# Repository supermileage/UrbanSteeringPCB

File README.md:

# Urban Steering PCB

The steering wheel for the UBC Supermileage Urban Concept electric vehicle is designed to steer the vehicle, provide information to the driver, and allow the driver to control the vehicle. This repo contains the design files for the printed circuit board at the core of the steering wheel. 

Some features of this PCB:

- STM32L432 Microcontroller with built-in CAN controller
- MCP 2562 CAN Transceiver
- 74HC595 and 74HC597 shift registers for LED output & button input
- ILI9341 3.2" LCD Screen
- Mechanical buttons with dual-color LEDs
- IR proximity sensor for dead man's switch functionality
- SD Card Reader
- Joystick

## Schematic

## Layout 

## Bill of Materials
Found on [Notion](https://www.notion.so/Bill-of-Materials-6644a4c081e64de49a3c111644f56321)

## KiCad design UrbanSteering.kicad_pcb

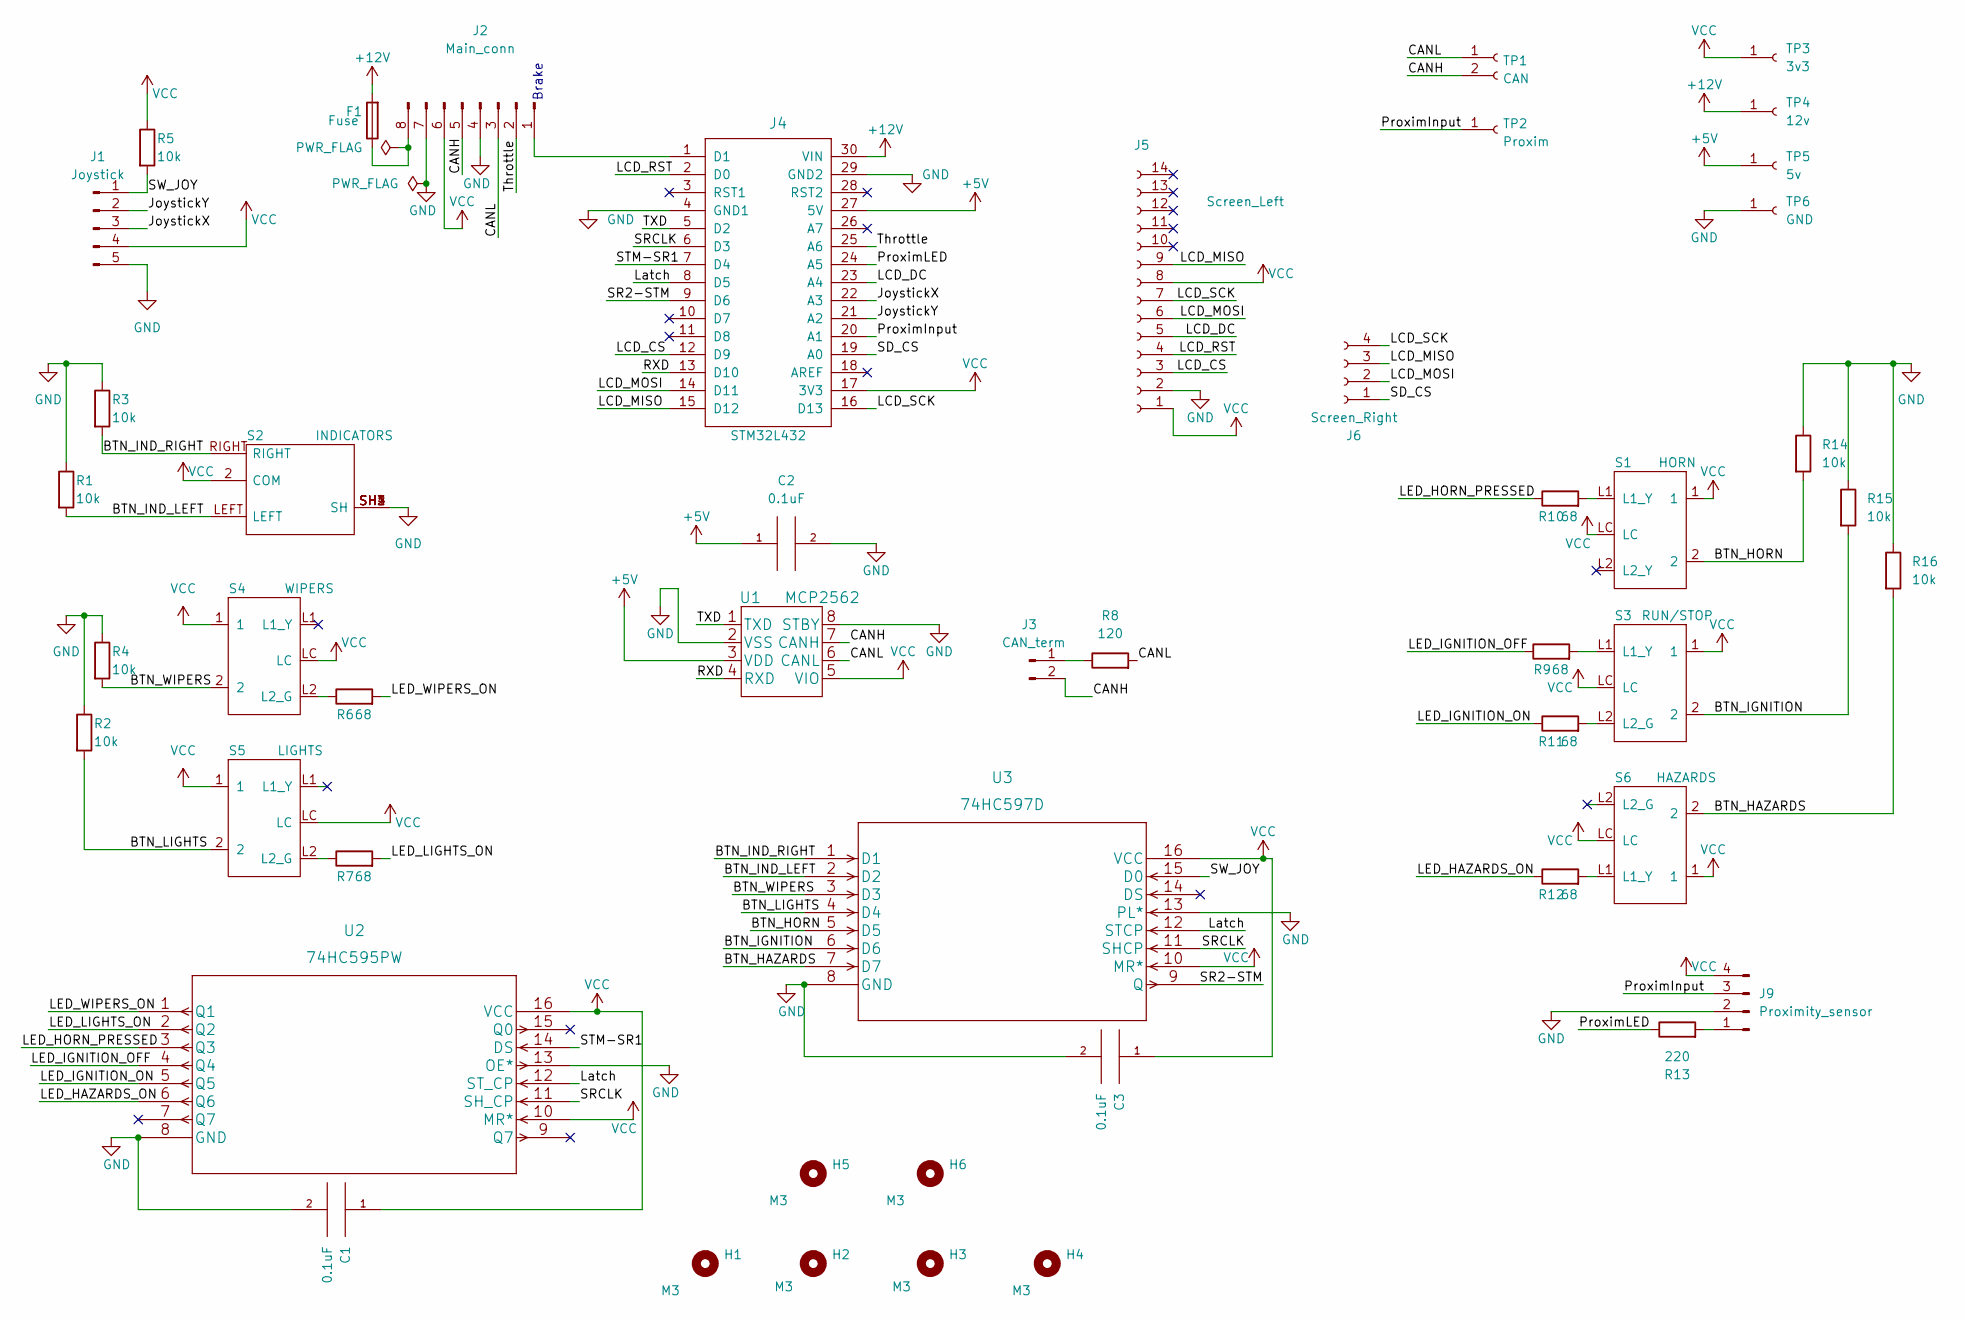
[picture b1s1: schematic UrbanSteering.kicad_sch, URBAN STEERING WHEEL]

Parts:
C1, C2, C3: 0.1uF; C_0805_2012Metric
F1: Fuse; Fuse_1206_3216Metric
H1, H2, H3, H4, H5, H6: M3; MountingHole_3.2mm_M3
J1: Joystick; PinHeader_1x05_P2.54mm_Vertical
J2: Main_conn; 705510007
J3: CAN_term; PinHeader_1x02_P2.54mm_Vertical
J4: STM32L432
J5: Screen_Left; PinHeader_1x14_P2.54mm_Vertical
J6: Screen_Right; PinHeader_1x04_P2.54mm_Vertical
J9: Proximity_sensor; 705510003
R1, R2, R3, R4, R5, R14, R15, R16: 10k; R_0805_2012Metric
R6, R7, R9, R10, R11, R12: 68; R_0805_2012Metric
R8: 120; R_0805_2012Metric
R13: 220; R_0805_2012Metric
S1: HORN; LP11OA1TCSYY
S2: INDICATORS; M2013TXG13DA
S3: RUN/STOP; LP11EE1NCSYG
S4: WIPERS; LP11EE1NCSYG
S5: LIGHTS; LP11EE1NCSYG
S6: HAZARDS; LP11EE1NCSYG
TP1: CAN; PinHeader_1x02_P2.54mm_Vertical
TP2: Proxim; PinHeader_1x01_P2.54mm_Vertical
TP3: 3v3; PinHeader_1x01_P2.54mm_Vertical
TP4: 12v; PinHeader_1x01_P2.54mm_Vertical
TP5: 5v; PinHeader_1x01_P2.54mm_Vertical
TP6: GND; PinHeader_1x01_P2.54mm_Vertical
U1: MCP2562; MCP2562FD-H&slash_P
U2: 74HC595PW; TSSOP-16-1EP_4.4x5mm_P0.65mm
U3: 74HC597D; TSSOP-16-1EP_4.4x5mm_P0.65mm

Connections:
+5V: C2.1, J4.27 (5V), TP5.1, U1.3 (VDD)
+12V: F1.2, J4.30 (VIN), TP4.1
/BTN_HAZARDS: R16.2, S6.2, U3.7 (D7)
/BTN_HORN: R14.2, S1.2, U3.5 (D5)
/BTN_IGNITION: R15.2, S3.2, U3.6 (D6)
/BTN_IND_LEFT: R1.2, S2.LEFT, U3.2 (D2)
/BTN_IND_RIGHT: R3.2, S2.RIGHT, U3.1 (D1)
/BTN_LIGHTS: R2.2, S5.2, U3.4 (D4)
/BTN_WIPERS: R4.2, S4.2, U3.3 (D3)
/CANH: J2.5, J3.2, TP1.2, U1.7 (CANH)
/CANL: J2.3, R8.2, TP1.1, U1.6 (CANL)
/JoystickX: J1.3, J4.22 (A3)
/JoystickY: J1.2, J4.21 (A2)
/LCD_CS: J4.12 (D9), J5.3
/LCD_DC: J4.23 (A4), J5.5
/LCD_MISO: J4.15 (D12), J5.9, J6.3
/LCD_MOSI: J4.14 (D11), J5.6, J6.2
/LCD_RST: J4.2 (D0), J5.4
/LCD_SCK: J4.16 (D13), J5.7, J6.4
/LED_HAZARDS_ON: R12.1, U2.6 (Q6)
/LED_HORN_PRESSED: R10.1, U2.3 (Q3)
/LED_IGNITION_OFF: R9.1, U2.4 (Q4)
/LED_IGNITION_ON: R11.1, U2.5 (Q5)
/LED_LIGHTS_ON: R7.2, U2.2 (Q2)
/LED_WIPERS_ON: R6.2, U2.1 (Q1)
/ProximInput: J4.20 (A1), J9.3, TP2.1; also elsewhere on the board
/ProximLED: J4.24 (A5), R13.1
/RXD: J4.13 (D10), U1.4 (RXD)
/SD_CS: J4.19 (A0), J6.1
/SR2-STM: J4.9 (D6), U3.9 (Q)
/SRCLK: J4.6 (D3), U2.11 (SH_CP), U3.11 (SHCP)
/STM-SR1: J4.7 (D4), U2.14 (DS)
/SW_JOY: J1.1, R5.2, U3.15 (D0)
/TXD: J4.5 (D2), U1.1 (TXD)
/Throttle: J2.2, J4.25 (A6)
unnamed: F1.1, J2.8
unnamed: J2.1, J4.1 (D1)
unnamed: J3.1, R8.1
unnamed: J9.1, R13.2
unnamed: R6.1, S4.L2 (L2_G)
unnamed: R7.1, S5.L2 (L2_G)
unnamed: R9.2, S3.L1 (L1_Y)
unnamed: R10.2, S1.L1 (L1_Y)
unnamed: R11.2, S3.L2 (L2_G)
unnamed: R12.2, S6.L1 (L1_Y)
VCC: C1.1, C3.1, J1.4, J2.6, J4.17 (3V3), J5.1, J5.8, J9.4, R5.1, S1.1, S1.LC, S2.2 (COM), S3.1, S3.LC, S4.1, S4.LC, S5.1, S5.LC, S6.1, S6.LC, TP3.1, U1.5 (VIO), U2.10 (MR*), U2.16 (VCC), U3.10 (MR*), U3.16 (VCC)

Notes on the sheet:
Brake

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
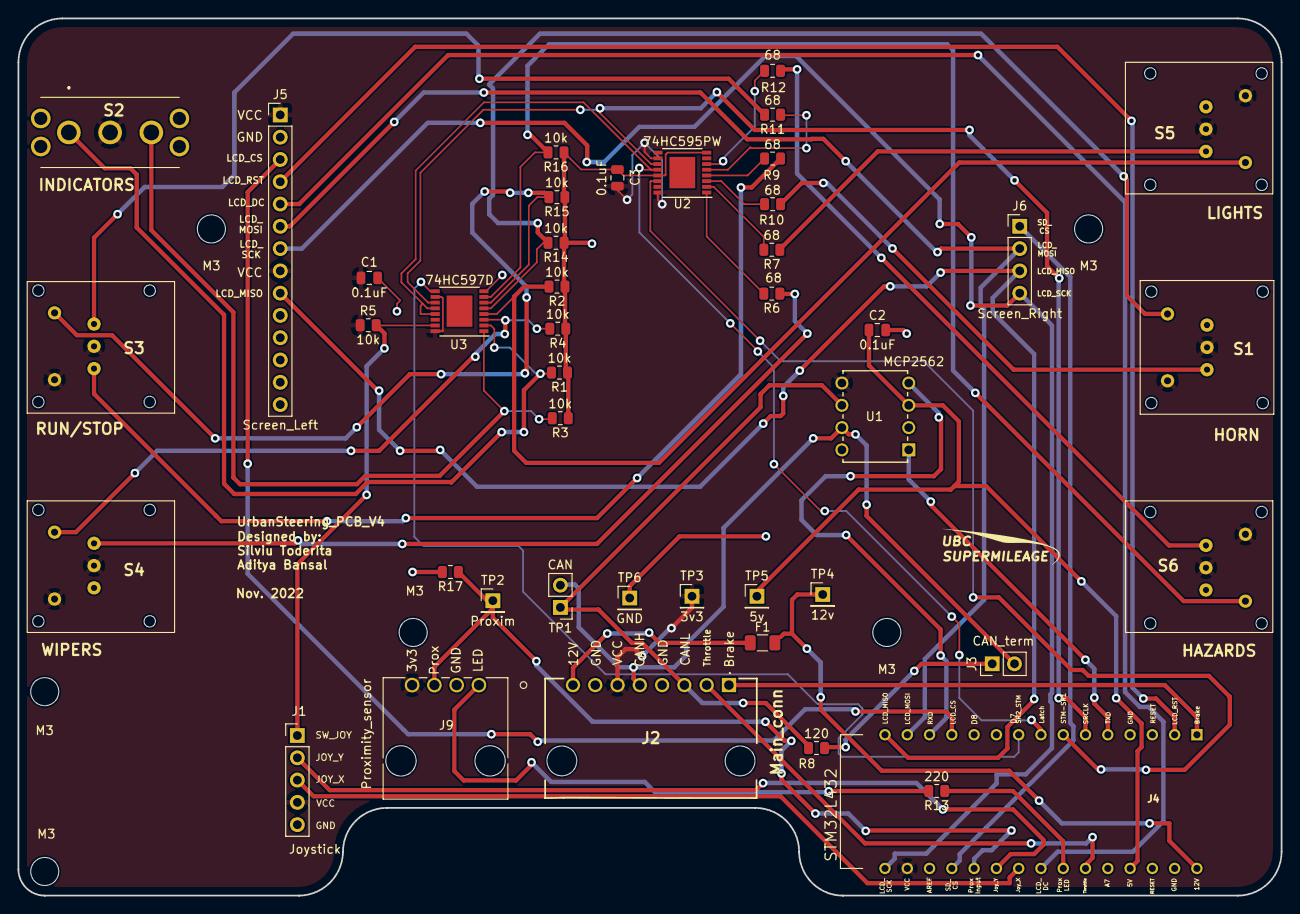
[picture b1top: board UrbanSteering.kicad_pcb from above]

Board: 2 copper layers, 144.0 x 100.0 mm, 50 parts (0 on the bottom side), 48 nets.

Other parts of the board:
R17: 10k; R_0805_2012Metric
SUPERMILEAGE: LOGO; Logo_bitmap

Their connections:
/ProximInput: R17.1; also elsewhere on the board

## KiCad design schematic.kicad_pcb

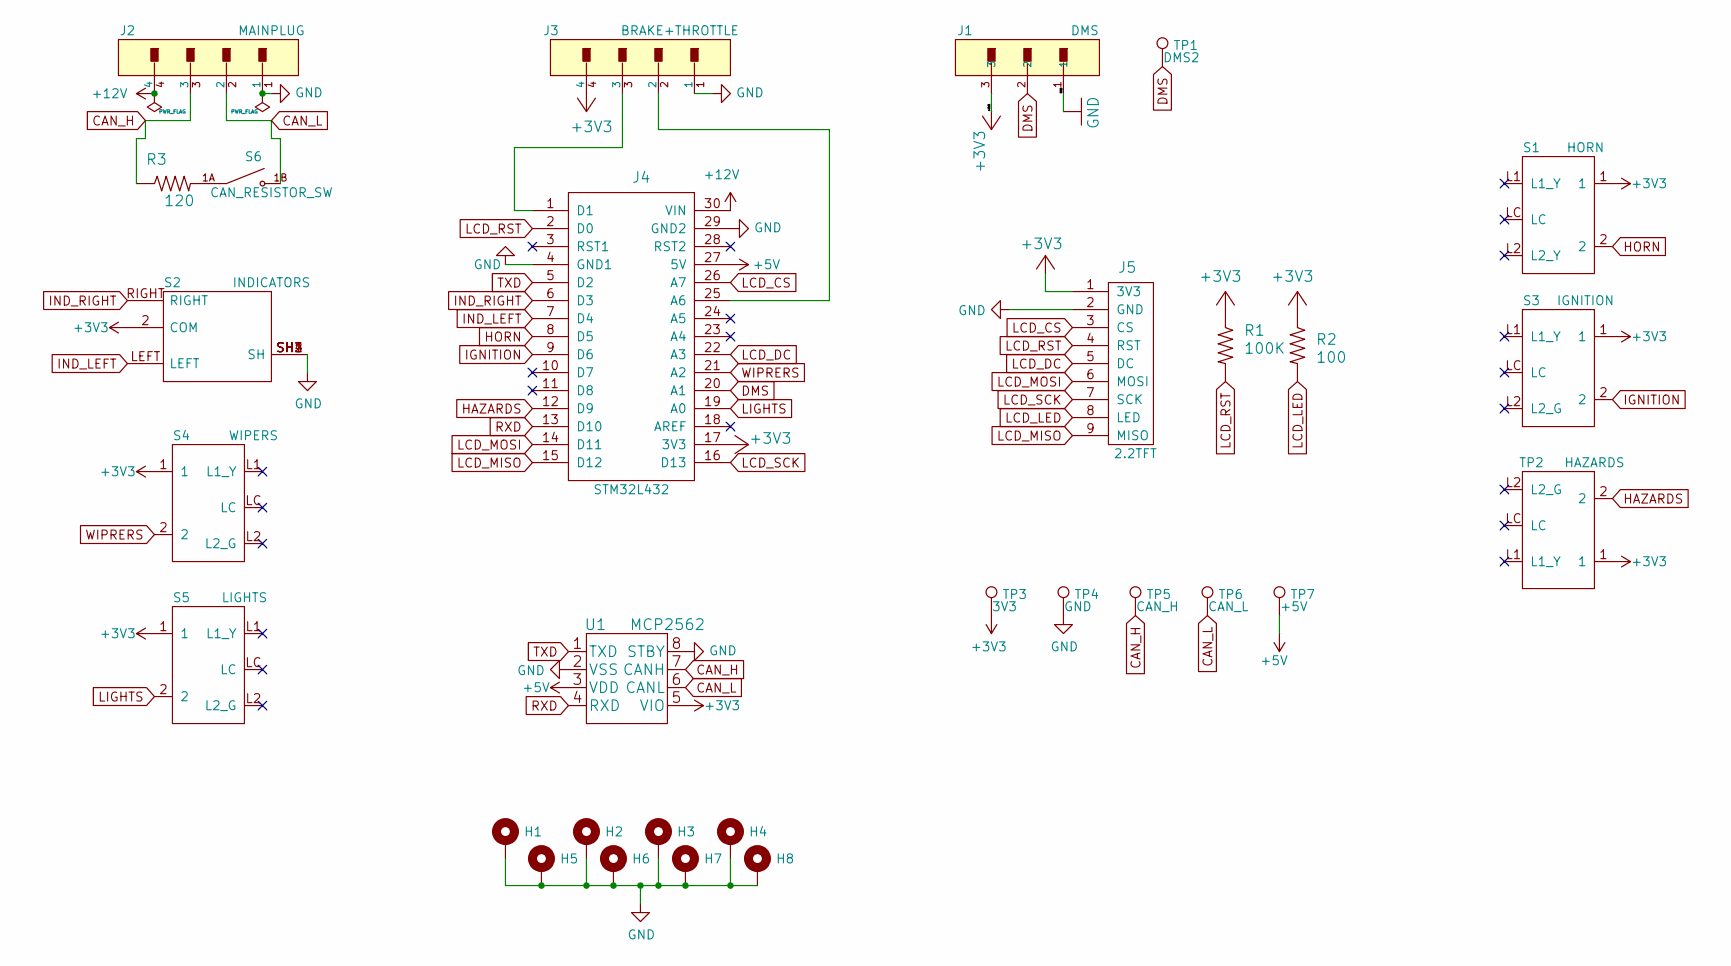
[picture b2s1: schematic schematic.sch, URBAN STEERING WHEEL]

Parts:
H1, H2, H3, H4, H5, H6, H7, H8: MountingHole_Pad; MountingHole_3.2mm_M3_Pad
J1: DMS; 15912035
J2: MAINPLUG; Molex-15-91-2045-0-0-0; current rating 3A; voltage rating 250V; mouser part number 538-15-91-2045; digikey description CONN HEADER 4POS .100 R/A SMD
J3: BRAKE+THROTTLE; Molex-15-91-2045-0-0-0; current rating 3A; voltage rating 250V; mouser part number 538-15-91-2045; digikey description CONN HEADER 4POS .100 R/A SMD
J4: STM32L432
J5: 2.2TFT
R1: 100K; RESC1608X55N
R2: 100; RESC1608X55N
R3: 120; RESC1608X55N
S1: HORN; LP11OA1TCSYY
S2: INDICATORS; M2013TXG13DA
S3: IGNITION; LP11EE1NCSYG
S4: WIPERS; LP11EE1NCSYG
S5: LIGHTS; LP11EE1NCSYG
S6: CAN_RESISTOR_SW; SW_DS04-254-2-01BK-SMT; PARTREV V0.0
TP1: DMS2; TestPoint_THTPad_D4.0mm_Drill2.0mm
TP2: HAZARDS; LP11EE1NCSYG
TP3: 3V3; TestPoint_THTPad_D4.0mm_Drill2.0mm
TP4: GND; TestPoint_THTPad_D4.0mm_Drill2.0mm
TP5: CAN_H; TestPoint_THTPad_D4.0mm_Drill2.0mm
TP6: CAN_L; TestPoint_THTPad_D4.0mm_Drill2.0mm
TP7: +5V; TestPoint_THTPad_D4.0mm_Drill2.0mm
U1: MCP2562; MCP2562FD-H&slash_P

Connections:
+3V3: J1.3, J3.4, J4.17 (3V3), J5.1 (3V3), R1.1, R2.1, S1.1, S2.2 (COM), S3.1, S4.1, S5.1, TP2.1, TP3.1, U1.5 (VIO)
+5V: J4.27 (5V), TP7.1, U1.3 (VDD)
+12V: J2.4, J4.30 (VIN)
CAN_H: J2.3, R3.1, TP5.1, U1.7 (CANH)
CAN_L: J2.2, S6.1B, TP6.1, U1.6 (CANL)
DMS: J1.2, J4.20 (A1), TP1.1
GND: H1.1, H2.1, H3.1, H4.1, H5.1, H6.1, H7.1, H8.1, J1.1, J2.1, J3.1, J4.4 (GND1), J4.29 (GND2), J5.2 (GND), S2.SH1 (SH), S2.SH2 (SH), S2.SH3 (SH), S2.SH4 (SH), TP4.1, U1.2 (VSS), U1.8 (STBY)
HAZARDS: J4.12 (D9), TP2.2
HORN: J4.8 (D5), S1.2
IGNITION: J4.9 (D6), S3.2
IND_LEFT: J4.7 (D4), S2.LEFT
IND_RIGHT: J4.6 (D3), S2.RIGHT
LCD_CS: J4.26 (A7), J5.3 (CS)
LCD_DC: J4.22 (A3), J5.5 (DC)
LCD_LED: J5.8 (LED), R2.2
LCD_MISO: J4.15 (D12), J5.9 (MISO)
LCD_MOSI: J4.14 (D11), J5.6 (MOSI)
LCD_RST: J4.2 (D0), J5.4 (RST), R1.2
LCD_SCK: J4.16 (D13), J5.7 (SCK)
LIGHTS: J4.19 (A0), S5.2
unnamed: J3.2, J4.25 (A6)
unnamed: J3.3, J4.1 (D1)
unnamed: R3.2, S6.1A
RXD: J4.13 (D10), U1.4 (RXD)
TXD: J4.5 (D2), U1.1 (TXD)
WIPRERS: J4.21 (A2), S4.2

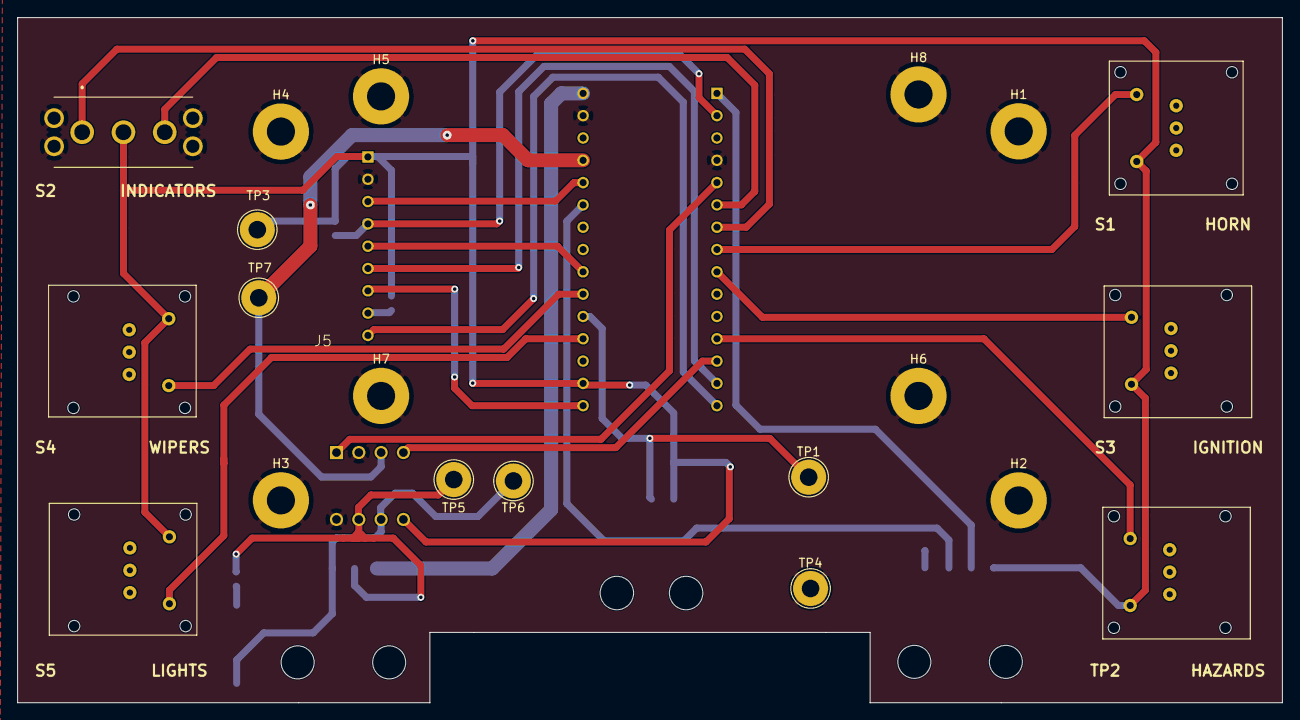
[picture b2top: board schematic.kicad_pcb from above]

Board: 2 copper layers, 144.0 x 78.0 mm, 30 parts (0 on the bottom side), 26 nets.

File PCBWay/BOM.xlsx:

Item # | Ref Des | Qty | Supplier | Mfg Part # | Description/Value | Package | Type | Note | Link
1.0 | J1 | 1.0 | Molex | 1.5912045E7 | SL 3 pin | 3-conn | SMD |  | https://www.digikey.ca/en/products/detail/molex/0015912035/5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
2.0 | J2, J3 | 2.0 | Moles | 1.5912045E7 | SL 4 pin | 4-conn | SMD |  | https://www.digikey.ca/en/products/detail/molex/0015912045/5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
3.0 | J4 | 2.0 | Sullins Connector Solutions | PPTC151LFBN-RC | female header (15pin) | 15pin | Thru hole | This is 2x - 15pin headers | https://www.digikey.ca/en/products/detail/sullins-connector-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
4.0 | J5 | 1.0 | Sullins Connector Solutions | PPTC091LFBN-RC | female header (9 pin) | 9pin | Thru hole |  | https://www.digikey.ca/en/products/detail/sullins-connector-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
5.0 | R1 | 1.0 | TE Connectivity Passive Product | RQ73C1J100KBTD | 100k | 0603 (1608metric) | SMD |  | https://www.digikey.ca/en/products/detail/te-connectivity-pa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
6.0 | R2 | 1.0 | TE Connectivity Passive Product | CRG0603F100R | 100 | 0604 (1608metric) | SMD |  | https://www.digikey.ca/en/products/detail/te-connectivity-pa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
7.0 | R3 | 1.0 | TE Connectivity Passive Product | CPF0603B120RE1 | 120 | 0605 (1608metric) | SMD |  | https://www.digikey.ca/en/products/detail/te-connectivity-pa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
8.0 | S1 | 1.0 | E-Switch | LP11OA1TCSYY | Push button (off-mom) |  | Thru hole |  | https://www.digikey.ca/en/products/detail/e-switch/LP11OA1TC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
9.0 | S2 | 1.0 | NKK Switches | M2013TXG13-DA | Rocker switch |  | Thru hole |  | https://www.digikey.ca/en/products/detail/nkk-switches/M2013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
10.0 | S3, S4, S5 | 3.0 | E-Switch | LP11EE1NCSYG | Push button (off-on) |  | Thru hole |  | https://www.digikey.ca/en/products/detail/e-switch/LP11EE1NC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
11.0 | S6 | 1.0 | CUI Devices | DS04-254-2-01BK-SMT | Dip switch (SPST) | Gullwing | SMD |  | https://www.digikey.ca/en/products/detail/cui-devices/DS04-2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
12.0 | U1 | 1.0 | Microchip Technology | MCP2562FD-H/P | CAN transiever | 8-PDIP | Thru hole |  | https://www.digikey.ca/en/products/detail/microchip-technolo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

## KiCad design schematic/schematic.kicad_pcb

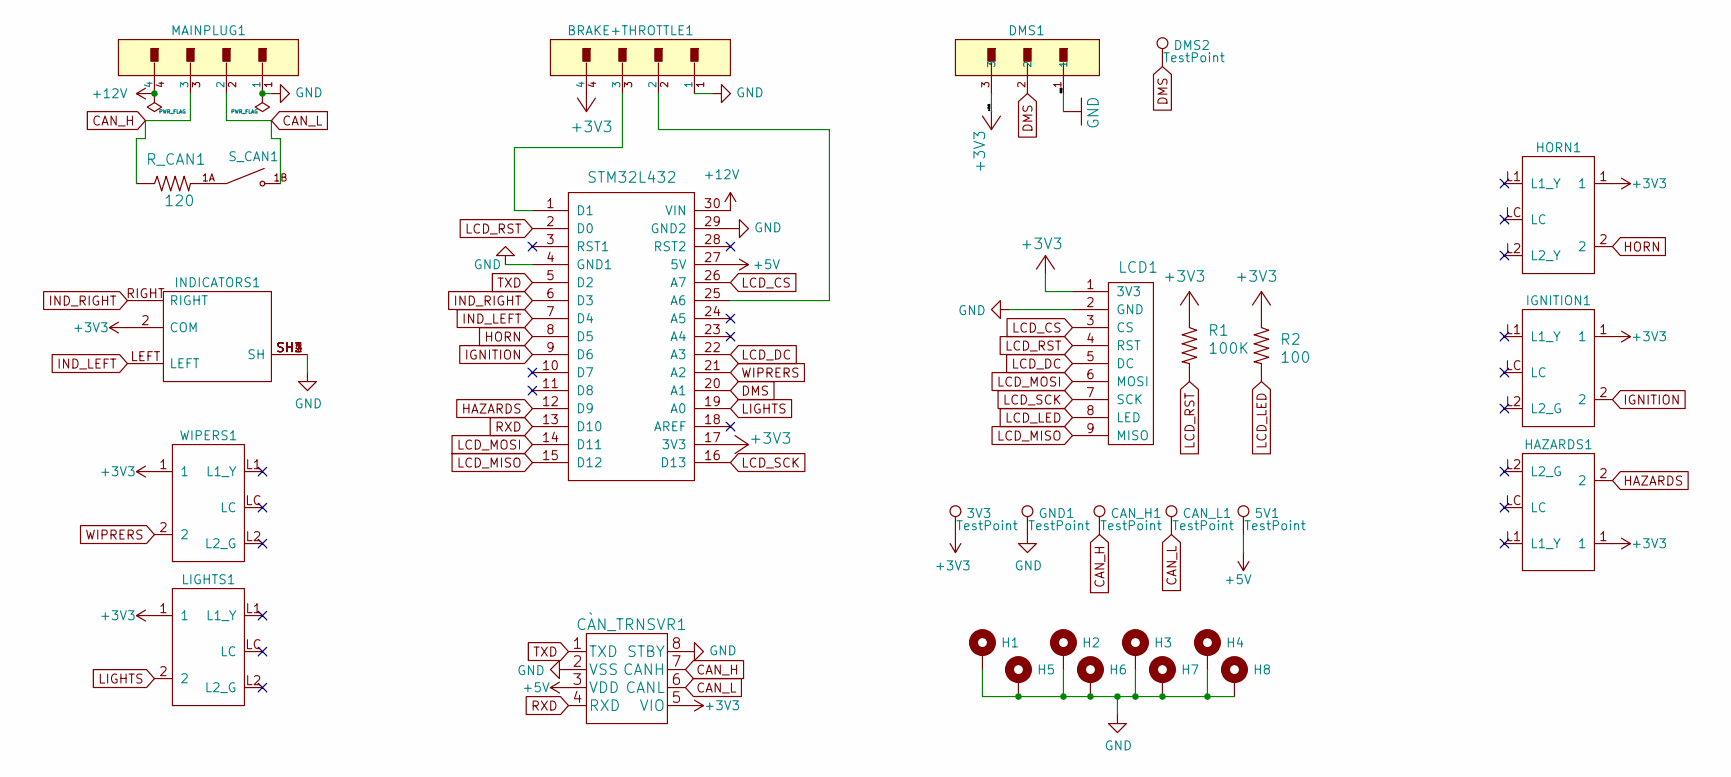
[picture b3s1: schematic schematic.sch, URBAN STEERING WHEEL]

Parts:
3V3, 5V1: TestPoint; TestPoint_THTPad_D4.0mm_Drill2.0mm
BRAKE+THROTTLE1: `; Molex-15-91-2045-0-0-0; current rating 3A; voltage rating 250V; mouser part number 538-15-91-2045; digikey description CONN HEADER 4POS .100 R/A SMD
CAN_H1: TestPoint; TestPoint_THTPad_D4.0mm_Drill2.0mm
CAN_L1: TestPoint; TestPoint_THTPad_D4.0mm_Drill2.0mm
CAN_TRNSVR1: `; MCP2562FD-H&slash_P
DMS1: `; 15912035
DMS2: TestPoint; TestPoint_THTPad_D4.0mm_Drill2.0mm
GND1: TestPoint; TestPoint_THTPad_D4.0mm_Drill2.0mm
H1, H2, H3, H4, H5, H6, H7, H8: MountingHole_Pad; MountingHole_3.2mm_M3_Pad
HAZARDS1: `; LP11EE1NCSYG
HORN1: `; LP11OA1TCSYY
IGNITION1: `; LP11EE1NCSYG
INDICATORS1: `; M2013TXG13DA
LCD1: 2.2TFT
LIGHTS1: `; LP11EE1NCSYG
MAINPLUG1: MOLEX-15-91-2045-PIN_HEADER; Molex-15-91-2045-0-0-0; current rating 3A; voltage rating 250V; mouser part number 538-15-91-2045; digikey description CONN HEADER 4POS .100 R/A SMD
R1: 100K; RESC1608X55N
R2: 100; RESC1608X55N
R_CAN1: 120; RESC1608X55N
STM32L432: STM32L432
S_CAN1: SW_DS04-254-2-01BK-SMT; PARTREV V0.0
WIPERS1: `; LP11EE1NCSYG

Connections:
+3V3: 3V3.1, BRAKE+THROTTLE1.4, CAN_TRNSVR1.5 (VIO), DMS1.3, HAZARDS1.1, HORN1.1, IGNITION1.1, INDICATORS1.2 (COM), LCD1.1 (3V3), LIGHTS1.1, R1.1, R2.1, STM32L432.17 (3V3), WIPERS1.1
+12V: MAINPLUG1.4, STM32L432.30 (VIN)
CAN_H: CAN_H1.1, CAN_TRNSVR1.7 (CANH), MAINPLUG1.3, R_CAN1.1
CAN_L: CAN_L1.1, CAN_TRNSVR1.6 (CANL), MAINPLUG1.2, S_CAN1.1B
DMS: DMS1.2, DMS2.1, STM32L432.20 (A1)
GND: BRAKE+THROTTLE1.1, CAN_TRNSVR1.2 (VSS), CAN_TRNSVR1.8 (STBY), DMS1.1, GND1.1, H1.1, H2.1, H3.1, H4.1, H5.1, H6.1, H7.1, H8.1, INDICATORS1.SH1 (SH), INDICATORS1.SH2 (SH), INDICATORS1.SH3 (SH), INDICATORS1.SH4 (SH), LCD1.2 (GND), MAINPLUG1.1, STM32L432.4 (GND1), STM32L432.29 (GND2)
HAZARDS: HAZARDS1.2, STM32L432.12 (D9)
HORN: HORN1.2, STM32L432.8 (D5)
IGNITION: IGNITION1.2, STM32L432.9 (D6)
IND_LEFT: INDICATORS1.LEFT, STM32L432.7 (D4)
IND_RIGHT: INDICATORS1.RIGHT, STM32L432.6 (D3)
LCD_CS: LCD1.3 (CS), STM32L432.26 (A7)
LCD_LED: LCD1.8 (LED), R2.2
LCD_MISO: LCD1.9 (MISO), STM32L432.15 (D12)
LCD_MOSI: LCD1.6 (MOSI), STM32L432.14 (D11)
LCD_RST: LCD1.4 (RST), R1.2, STM32L432.2 (D0)
LCD_SCK: LCD1.7 (SCK), STM32L432.16 (D13)
LIGHTS: LIGHTS1.2, STM32L432.19 (A0)
unnamed: BRAKE+THROTTLE1.2, STM32L432.25 (A6)
unnamed: BRAKE+THROTTLE1.3, STM32L432.1 (D1)
unnamed: R_CAN1.2, S_CAN1.1A
RXD: CAN_TRNSVR1.4 (RXD), STM32L432.13 (D10)
TXD: CAN_TRNSVR1.1 (TXD), STM32L432.5 (D2)
WIPRERS: STM32L432.21 (A2), WIPERS1.2

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
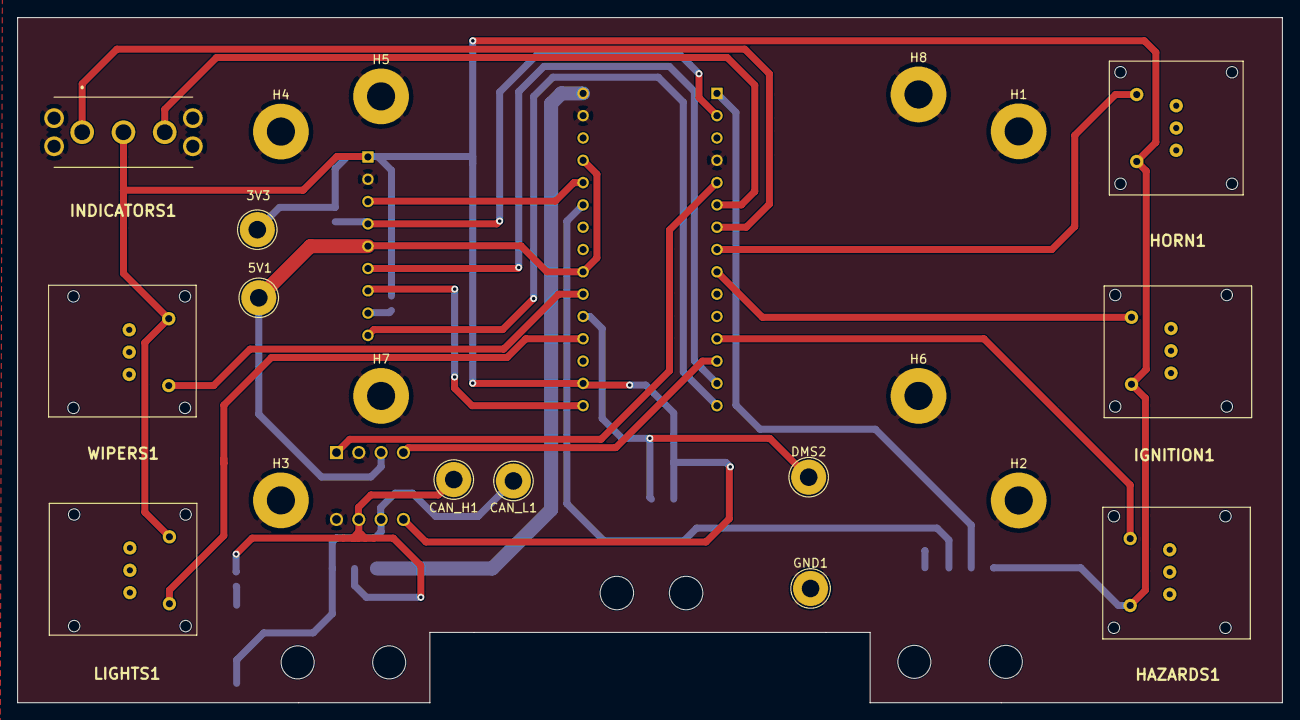
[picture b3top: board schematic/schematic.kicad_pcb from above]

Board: 2 copper layers, 144.0 x 78.0 mm, 30 parts (0 on the bottom side), 25 nets.

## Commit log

2020-11-27 ALMOST DONE, ROUTING LEFT
2020-12-04 V3 done design review pending
2020-12-08 EVERYTHING COMPLETE POST DESIGN REVIEW
2021-01-04 Cleaned up labels and fixed DRC warnings
2021-01-04 Cleaned file structure
2021-01-05 Cleaned up project structure, schematic and mask. Changed the DC connection for the TFT
2021-01-10 Generated fab files
2021-01-10 Removed accidental file
2021-01-10 Added README
2021-01-20 Cleaned up, added to readme, added images, new outputs
2021-01-20 Removed old files
2022-10-23 added components and started wiring
2022-11-03 PCB version 4
2022-11-05 PCB version-4 with mounting holes
2022-11-05 started pcb layout
2022-11-07 PCB version-4 layout 1.0
2022-11-07 PCB version 4 layout 2.0
2022-11-07 PCB version 4 layout 3.0
2022-11-07 adjusts position of some footprints, adds most required labels, deletes existing traces, flips LCD orientation, and adjusts netclass sizes
2022-11-07 makes bottom filled zone GND and adds some connections from top SMD component grounds
2022-11-09 added top filled zone for VCC
2022-11-09 added labels and tracing... Some errors on DRC
2022-11-10 updated clearance settings and connected some non-contiguous filled zones
2022-11-10 added label names on STM
2022-11-26 added fuse to schematic - layout to be changed
2022-11-27 added labels
2022-11-29 made capacitor and stm shifting change, also edited main connector labels
2022-11-30 made all changes
2022-12-01 adds output files
2022-12-03 added images
2022-12-03 images
2022-12-03 README latest update
2023-02-06 Physical hardware changes replicated in KiCad design
2023-08-22 updates readme

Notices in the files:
parts and their libraries:
Copyright 2016 Accelerated Designs. All rights reserved.
Copyright 2021 Accelerated Designs. All rights reserved.
